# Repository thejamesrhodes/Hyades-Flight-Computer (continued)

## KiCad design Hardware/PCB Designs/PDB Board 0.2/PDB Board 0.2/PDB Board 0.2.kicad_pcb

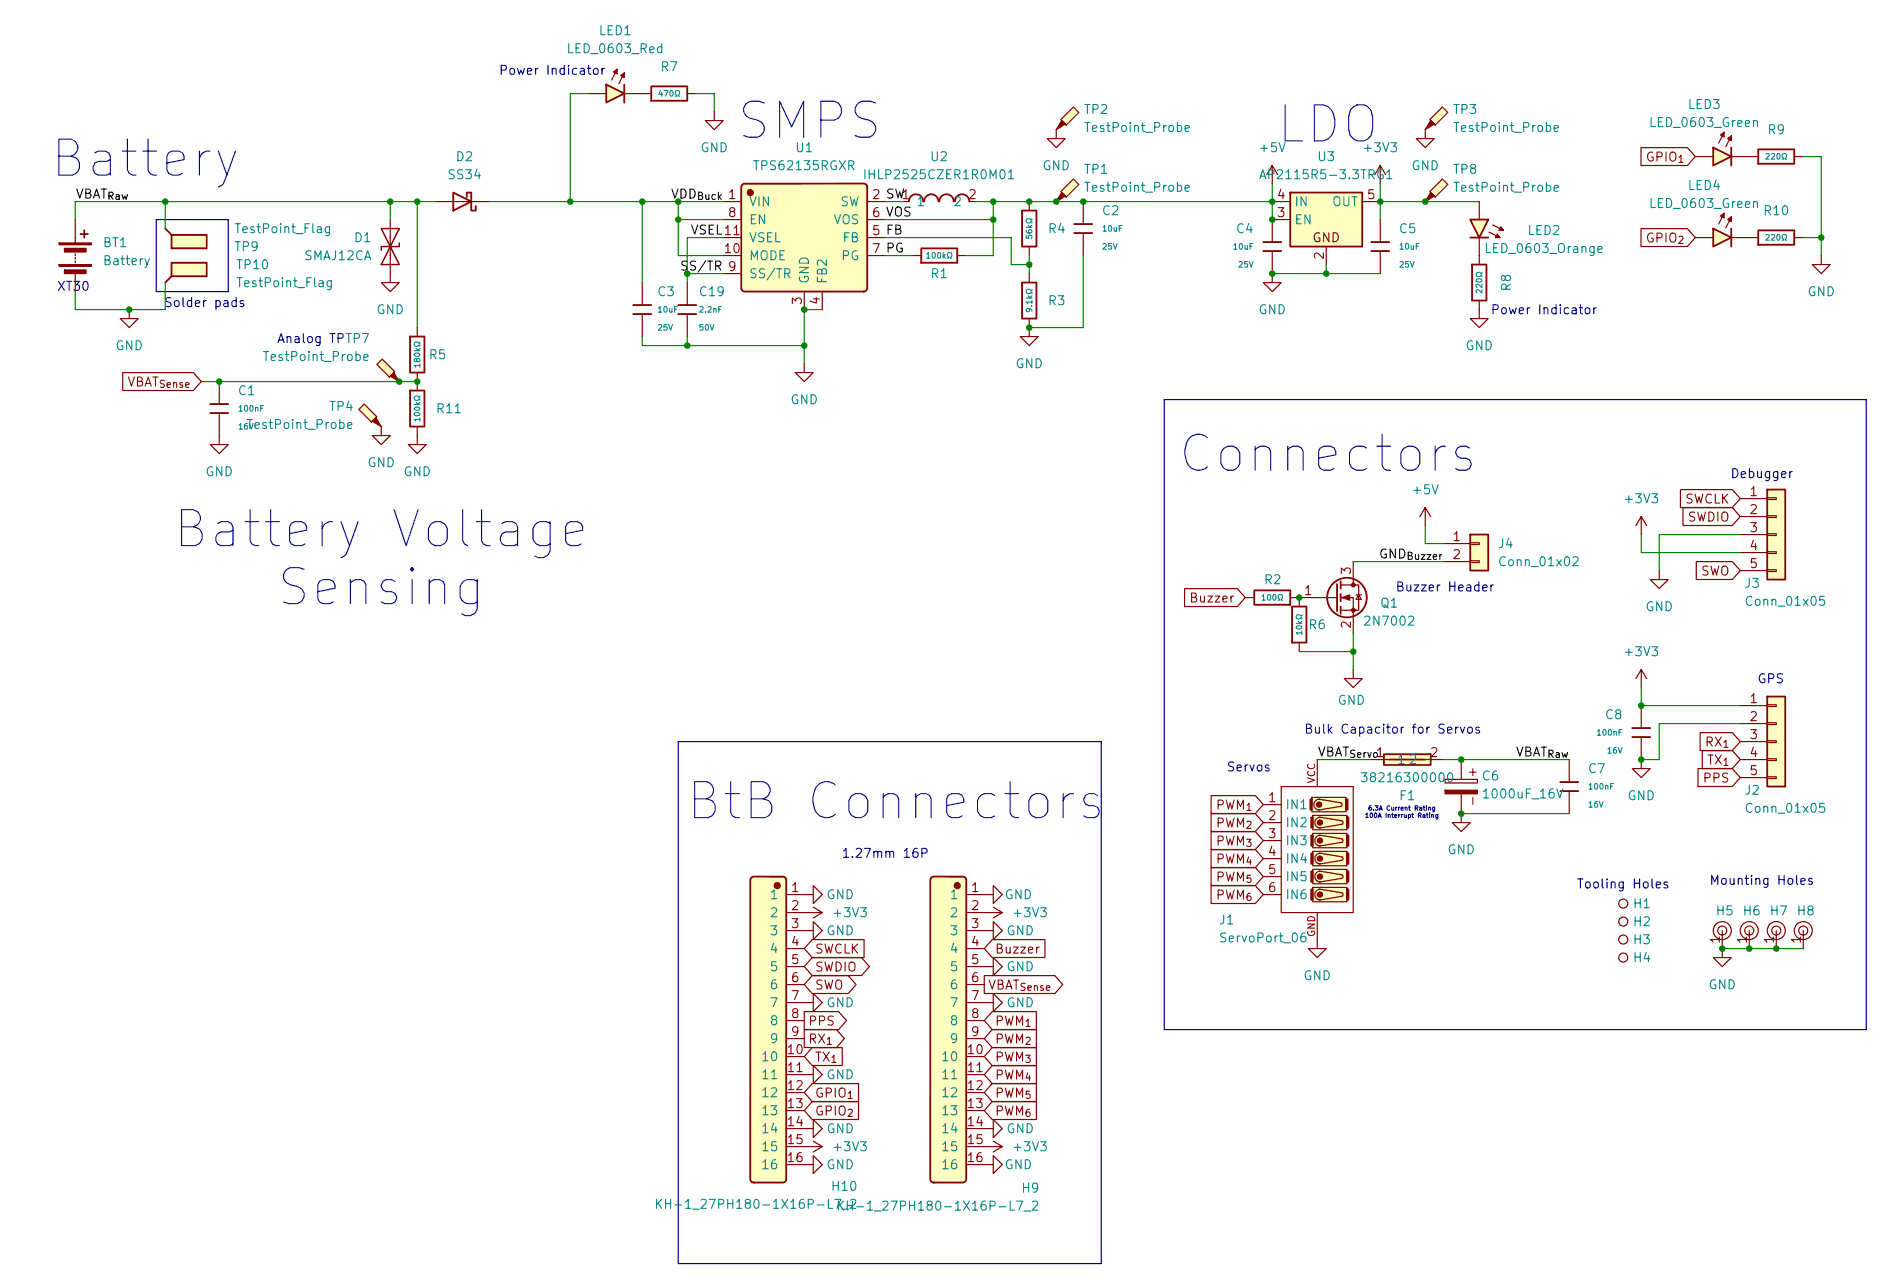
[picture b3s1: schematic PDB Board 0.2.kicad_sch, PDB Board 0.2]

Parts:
BT1: Battery; AMASS_XT30UPB-F_1x02_P5.0mm_Vertical
C1, C7, C8: 100nF; C_0402; Voltage Rated 16V; Tolerance ±10%; Part CL05B104KO5NNNC; LCSC C1525
C2, C3, C4, C5: 10uF; C_0805; Voltage Rated 25V; Tolerance ±10%; Part CL21A106KAYNNNE; LCSC C15850
C6: 1000uF_16V; CP_Radial_D10.0mm_P5.00mm
C19: 2.2nF; C_0402; Voltage Rated 50V; Tolerance ±10%; Part 0402B222K500NT; LCSC C1531
D1: SMAJ12CA; D_SMA
D2: SS34; D_SMA
F1: 38216300000; Manufacturer Part 38216300000; LCSC C142713
H1, H2, H3, H4: Hole_Tooling_JLCPCB
H5, H6, H7, H8: Hole, 3mm
H9, H10: KH-1_27PH180-1X16P-L7_2; Manufacturer Part KH-1.27PH180-1X16P-L7.2; LCSC C2938407
J1: ServoPort_06; ServoPort_06_Vertical
J2, J3: Conn_01x05; JST_XH_B5B-XH-A_1x05_P2.50mm_Vertical
J4: Conn_01x02; JST_XH_B2B-XH-A_1x02_P2.50mm_Vertical; Part Number 1-0201FBV0T
LED1: LED_0603_Red; LED_0603_1608Metric
LED2: LED_0603_Orange; LED_0603_1608Metric
LED3, LED4: LED_0603_Green; LED_0603_1608Metric
Q1: 2N7002; SOT-23
R1, R11: 100kΩ; R_0402; Overload Voltage (Max) 50V; Tolerance ±1%; Part 0402WGF1003TCE; LCSC C25741
R2: 100Ω; R_0402; Overload Voltage (Max) 50V; Tolerance ±1%; Part 0402WGF1000TCE; LCSC C25076
R3: 9.1kΩ; R_0603; Overload Voltage (Max) 75V; Tolerance ±1%; Part 0603WAF9101T5E; LCSC C23260
R4: 56kΩ; R_0603; Overload Voltage (Max) 75V; Tolerance ±1%; Part 0603WAF5602T5E; LCSC C23206
R5: 180kΩ; R_0603; Overload Voltage (Max) 75V; Tolerance ±1%; Part 0603WAF1803T5E; LCSC C22827
R6: 10kΩ; R_0402; Overload Voltage (Max) 50V; Tolerance ±1%; Part 0402WGF1002TCE; LCSC C25744
R7: 470Ω; R_0402; Overload Voltage (Max) 50V; Tolerance ±1%; Part 0402WGF4700TCE; LCSC C25117
R8, R9, R10: 220Ω; R_0402; Overload Voltage (Max) 50V; Tolerance ±1%; Part 0402WGF2200TCE; LCSC C25091
TP1, TP2, TP3, TP4, TP7, TP8: TestPoint_Probe; TestPoint_Pad_04
TP9, TP10: TestPoint_Flag; SolderWirePad_1x01_SMD_4x8mm
U1: TPS62135RGXR; Manufacturer Part TPS62135RGXR; LCSC C167238
U2: IHLP2525CZER1R0M01; Manufacturer Part IHLP2525CZER1R0M01; LCSC C845018
U3: AP2115R5-3.3TRG1; Diodes_SOT-89-5

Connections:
+3V3: C5.1, C8.1, H9.2, H9.15, H10.2, H10.15, J2.1, J3.4, LED2.2 (A), TP8.1 (1_1), U3.5 (OUT)
+5V: C2.1, C4.1, J4.1, R1.2, R4.1, TP1.1 (1_1), U1.6 (VOS), U2.2, U3.3 (EN), U3.4 (IN)
/FB: R3.1, R4.2, U1.5 (FB)
/GND_{Buzzer}: J4.2, Q1.3 (D)
/PG: R1.1, U1.7 (PG)
/SS/TR: C19.1, U1.9 (SS/TR), U1.11 (VSEL)
/SW: U1.2 (SW), U2.1
/VBAT_{Raw}: BT1.1 (+), C6.1, C7.1, D1.2 (A2), D2.2 (A), F1.2, R5.1, TP9.1 (1_1)
/VBAT_{Servo}: F1.1, J1.VCC
/VDD_{Buck}: C3.1, D2.1 (K), LED1.2 (A), U1.1 (VIN), U1.8 (EN), U1.10 (MODE)
Buzzer: H9.4, R2.2
GND: BT1.2 (-), C1.2, C2.2, C3.2, C4.2, C5.2, C6.2, C7.2, C8.2, C19.2, D1.1 (A1), H5.1, H6.1, H7.1, H8.1, H9.1, H9.3, H9.5, H9.7, H9.14, H9.16, H10.1, H10.3, H10.7, H10.11, H10.14, H10.16, J1.GND, J2.2, J3.3, Q1.2 (S), R3.2, R6.1, R7.2, R8.2, R9.2, R10.2, R11.2, TP2.1 (1_1), TP3.1 (1_1), TP4.1 (1_1), TP10.1 (1_1), U1.3 (GND), U1.4 (FB2), U3.2
GPIO_{1}: H10.12, LED3.2 (A)
GPIO_{2}: H10.13, LED4.2 (A)
unnamed: LED1.1 (K), R7.1
unnamed: LED2.1 (K), R8.1
unnamed: LED3.1 (K), R9.1
unnamed: LED4.1 (K), R10.1
unnamed: Q1.1 (G), R2.1, R6.2
PPS: H10.8, J2.5
PWM_{1}: H9.8, J1.1 (IN1)
PWM_{2}: H9.9, J1.2 (IN2)
PWM_{3}: H9.10, J1.3 (IN3)
PWM_{4}: H9.11, J1.4 (IN4)
PWM_{5}: H9.12, J1.5 (IN5)
PWM_{6}: H9.13, J1.6 (IN6)
RX_{1}: H10.9, J2.3
SWCLK: H10.4, J3.1
SWDIO: H10.5, J3.2
SWO: H10.6, J3.5
TX_{1}: H10.10, J2.4
VBAT_{Sense}: C1.1, H9.6, R5.2, R11.1, TP7.1 (1_1)

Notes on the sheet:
Solder pads
BtB Connectors
XT30
6.3A Current Rating 100A Interrupt Rating
Servos
SMPS
Power Indicator
Bulk Capacitor for Servos
Connectors
Analog TP
1.27mm 16P
Mounting Holes
LDO
Battery
Buzzer Header
Battery Voltage Sensing
GPS
Debugger
Tooling Holes

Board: 4 copper layers, 54 parts (2 on the bottom side), 32 nets, no tracks yet.

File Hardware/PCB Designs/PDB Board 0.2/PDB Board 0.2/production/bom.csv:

Designator,Footprint,Quantity,Value,LCSC Part #
BT1,AMASS_XT30UPB-F_1x02_P5.0mm_Vertical,1,Battery,
"C1, C7, C8",C_0402,3,100nF,C1525
C19,C_0402,1,2.2nF,C1531
"C2, C3, C4, C5",C_0805,4,10uF,C15850
C6,CP_Radial_D10.0mm_P5.00mm,1,1000uF_16V,
D1,D_SMA,1,SMAJ12CA,
D2,D_SMA,1,SS34,
F1,38216300000,1,38216300000,C142713
"H1, H2, H3, H4",Hole_Tooling_JLCPCB,4,~,
"H10, H9",KH-1_27PH180-1X16P-L7_2,2,KH-1_27PH180-1X16P-L7_2,C2938407
"H5, H6, H7, H8","Hole, 3mm",4,~,
J1,ServoPort_06_Vertical,1,ServoPort_06,
"J2, J3",JST_XH_B5B-XH-A_1x05_P2.50mm_Vertical,2,Conn_01x05,
J4,JST_XH_B2B-XH-A_1x02_P2.50mm_Vertical,1,Conn_01x02,
LED1,0603,1,LED_0603_Red,
LED2,0603,1,LED_0603_Orange,
"LED3, LED4",0603,2,LED_0603_Green,
Q1,SOT-23,1,2N7002,
"R1, R11",R_0402,2,100kΩ,C25741
"R10, R8, R9",R_0402,3,220Ω,C25091
R2,R_0402,1,100Ω,C25076
R3,R_0603,1,9.1kΩ,C23260
R4,R_0603,1,56kΩ,C23206
R5,R_0603,1,180kΩ,C22827
R6,R_0402,1,10kΩ,C25744
R7,R_0402,1,470Ω,C25117
"TP1, TP2, TP3, TP4, TP7, TP8",TestPoint_Pad_04,6,TestPoint_Probe,
"TP10, TP9",SolderWirePad_1x01_SMD_4x8mm,2,TestPoint_Flag,
U1,TPS62135RGXR,1,TPS62135RGXR,C167238
U2,IHLP2525CZER1R0M01,1,IHLP2525CZER1R0M01,C845018
U4,Diodes_SOT-89-5,1,AP2115R5A-3.3TRG1,

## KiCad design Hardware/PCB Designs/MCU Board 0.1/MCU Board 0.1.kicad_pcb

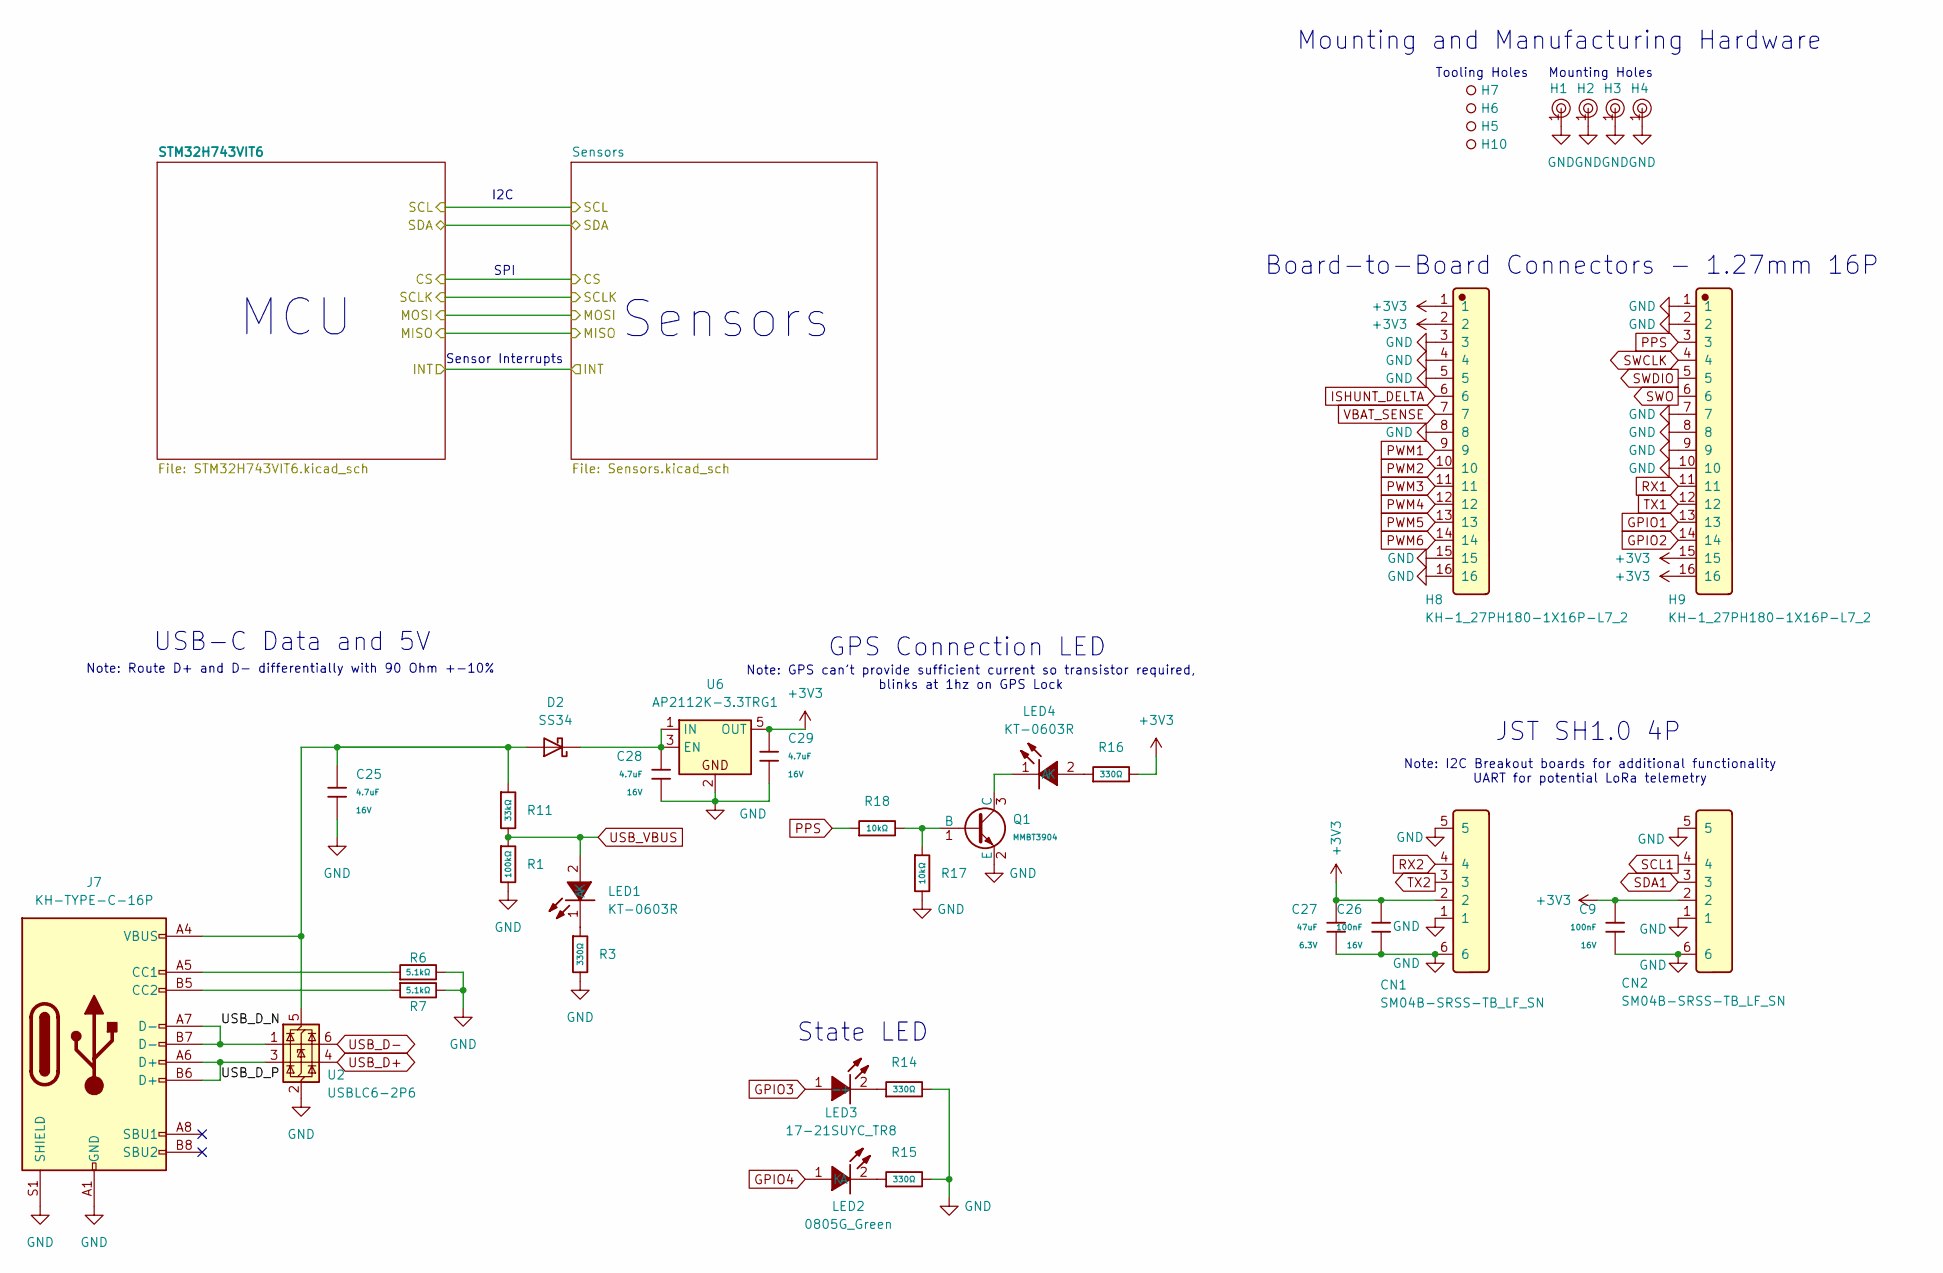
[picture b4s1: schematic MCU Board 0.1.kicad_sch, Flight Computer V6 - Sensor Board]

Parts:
C9, C26: 100nF; C_0402; Voltage Rated 16V; Tolerance ±10%; Part CL05B104KO5NNNC; LCSC C1525
C25, C28, C29: 4.7uF; C_0603; Voltage Rated 16V; Tolerance ±10%; Part CL10A475KO8NNNC; LCSC C19666
C27: 47uF; C_0805; Voltage Rated 6.3V; Tolerance ±20%; Part CL21A476MQYNNNE; LCSC C16780
CN1, CN2: SM04B-SRSS-TB_LF_SN; Manufacturer Part SM04B-SRSS-TB(LF)(SN); LCSC C160404
D2: SS34; D_SMA
H1, H2, H3, H4: Hole, 3mm
H5, H6, H7, H10: Hole_Tooling_JLCPCB
H8, H9: KH-1_27PH180-1X16P-L7_2; Manufacturer Part KH-1.27PH180-1X16P-L7.2; LCSC C2938407
J7: KH-TYPE-C-16P
LED1, LED4: KT-0603R; Manufacturer Part KT-0603R; LCSC C2286
LED2: 0805G_Green; Manufacturer Part KT-0805G; LCSC C2297
LED3: 17-21SUYC_TR8; Manufacturer Part KT-0805黄灯; LCSC C2296
Q1: MMBT3904; Q_SOT-23; Part MMBT3904; LCSC C7420353
R1: 100kΩ; R_0402; Overload Voltage (Max) 50V; Tolerance ±1%; Part 0402WGF1003TCE; LCSC C25741
R3, R14, R15, R16: 330Ω; R_0402; Overload Voltage (Max) 50V; Tolerance ±1%; Part 0402WGF3300TCE; LCSC C25104
R6, R7: 5.1kΩ; R_0402; Overload Voltage (Max) 50V; Tolerance ±1%; Part 0402WGF5101TCE; LCSC C25905
R11: 33kΩ; R_0402; Overload Voltage (Max) 50V; Tolerance ±1%; Part 0402WGF3302TCE; LCSC C25779
R17, R18: 10kΩ; R_0402; Overload Voltage (Max) 50V; Tolerance ±1%; Part 0402WGF1002TCE; LCSC C25744
U2: USBLC6-2P6; SOT-666
U6: AP2112K-3.3TRG1; SOT-23-5

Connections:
+3V3: C9.1, C26.1, C27.1, C29.1, CN1.2, CN2.2, H8.1, H8.2, H9.15, H9.16, R16.2, U6.5 (OUT); also elsewhere on the board
/USB_D_N: J7.A7 (D-), J7.B7 (D-), U2.1 (I/O1)
/USB_D_P: J7.A6 (D+), J7.B6 (D+), U2.3 (I/O2)
GND: C9.2, C25.2, C26.2, C27.2, C28.2, C29.2, CN1.1, CN1.5, CN1.6, CN2.1, CN2.5, CN2.6, H1.1, H2.1, H3.1, H4.1, H8.3, H8.4, H8.5, H8.8, H8.15, H8.16, H9.1, H9.2, H9.7, H9.8, H9.9, H9.10, J7.A1 (GND), J7.A12 (GND), J7.B1 (GND), J7.B12 (GND), J7.S1 (SHIELD), Q1.2 (E), R1.2, R3.2, R6.2, R7.2, R14.2, R15.2, R17.2, U2.2 (GND), U6.2; also elsewhere on the board
GPIO1: H9.13; also elsewhere on the board
GPIO2: H9.14; also elsewhere on the board
GPIO3: LED3.1 (+); also elsewhere on the board
GPIO4: LED2.1 (A); also elsewhere on the board
ISHUNT_DELTA: H8.6; also elsewhere on the board
unnamed: C25.1, D2.2 (A), J7.A4 (VBUS), J7.A9 (VBUS), J7.B4 (VBUS), J7.B9 (VBUS), R11.1, U2.5 (VBUS)
unnamed: C28.1, D2.1 (K), U6.1 (IN), U6.3 (EN)
unnamed: J7.A5 (CC1), R6.1
unnamed: J7.B5 (CC2), R7.1
unnamed: LED1.1 (K), R3.1
unnamed: LED2.2 (K), R15.1
unnamed: LED3.2 (-), R14.1
unnamed: LED4.2 (A), R16.1
unnamed: LED4.1 (K), Q1.3 (C)
unnamed: Q1.1 (B), R17.1, R18.2
PPS: H9.3, R18.1; also elsewhere on the board
PWM1: H8.9; also elsewhere on the board
PWM2: H8.10; also elsewhere on the board
PWM3: H8.11; also elsewhere on the board
PWM4: H8.12; also elsewhere on the board
PWM5: H8.13; also elsewhere on the board
PWM6: H8.14; also elsewhere on the board
RX1: H9.11; also elsewhere on the board
RX2: CN1.4; also elsewhere on the board
SCL1: CN2.4; also elsewhere on the board
SDA1: CN2.3; also elsewhere on the board
SWCLK: H9.4; also elsewhere on the board
SWDIO: H9.5; also elsewhere on the board
SWO: H9.6; also elsewhere on the board
TX1: H9.12; also elsewhere on the board
TX2: CN1.3; also elsewhere on the board
USB_D+: U2.4 (I/O2); also elsewhere on the board
USB_D-: U2.6 (I/O1); also elsewhere on the board
USB_VBUS: LED1.2 (A), R1.1, R11.2; also elsewhere on the board
VBAT_SENSE: H8.7; also elsewhere on the board

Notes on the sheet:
Tooling Holes
Sensor Interrupts
Sensors
Board-to-Board Connectors - 1.27mm 16P
GPS Connection LED
State LED
USB-C Data and 5V
Note: Route D+ and D- differentially with 90 Ohm +-10%
Note: GPS can't provide sufficient current so transistor required, blinks at 1hz on GPS Lock
JST SH1.0 4P
Note: I2C Breakout boards for additional functionality UART for potential LoRa telemetry
SPI
I2C
Mounting and Manufacturing Hardware
Mounting Holes
MCU

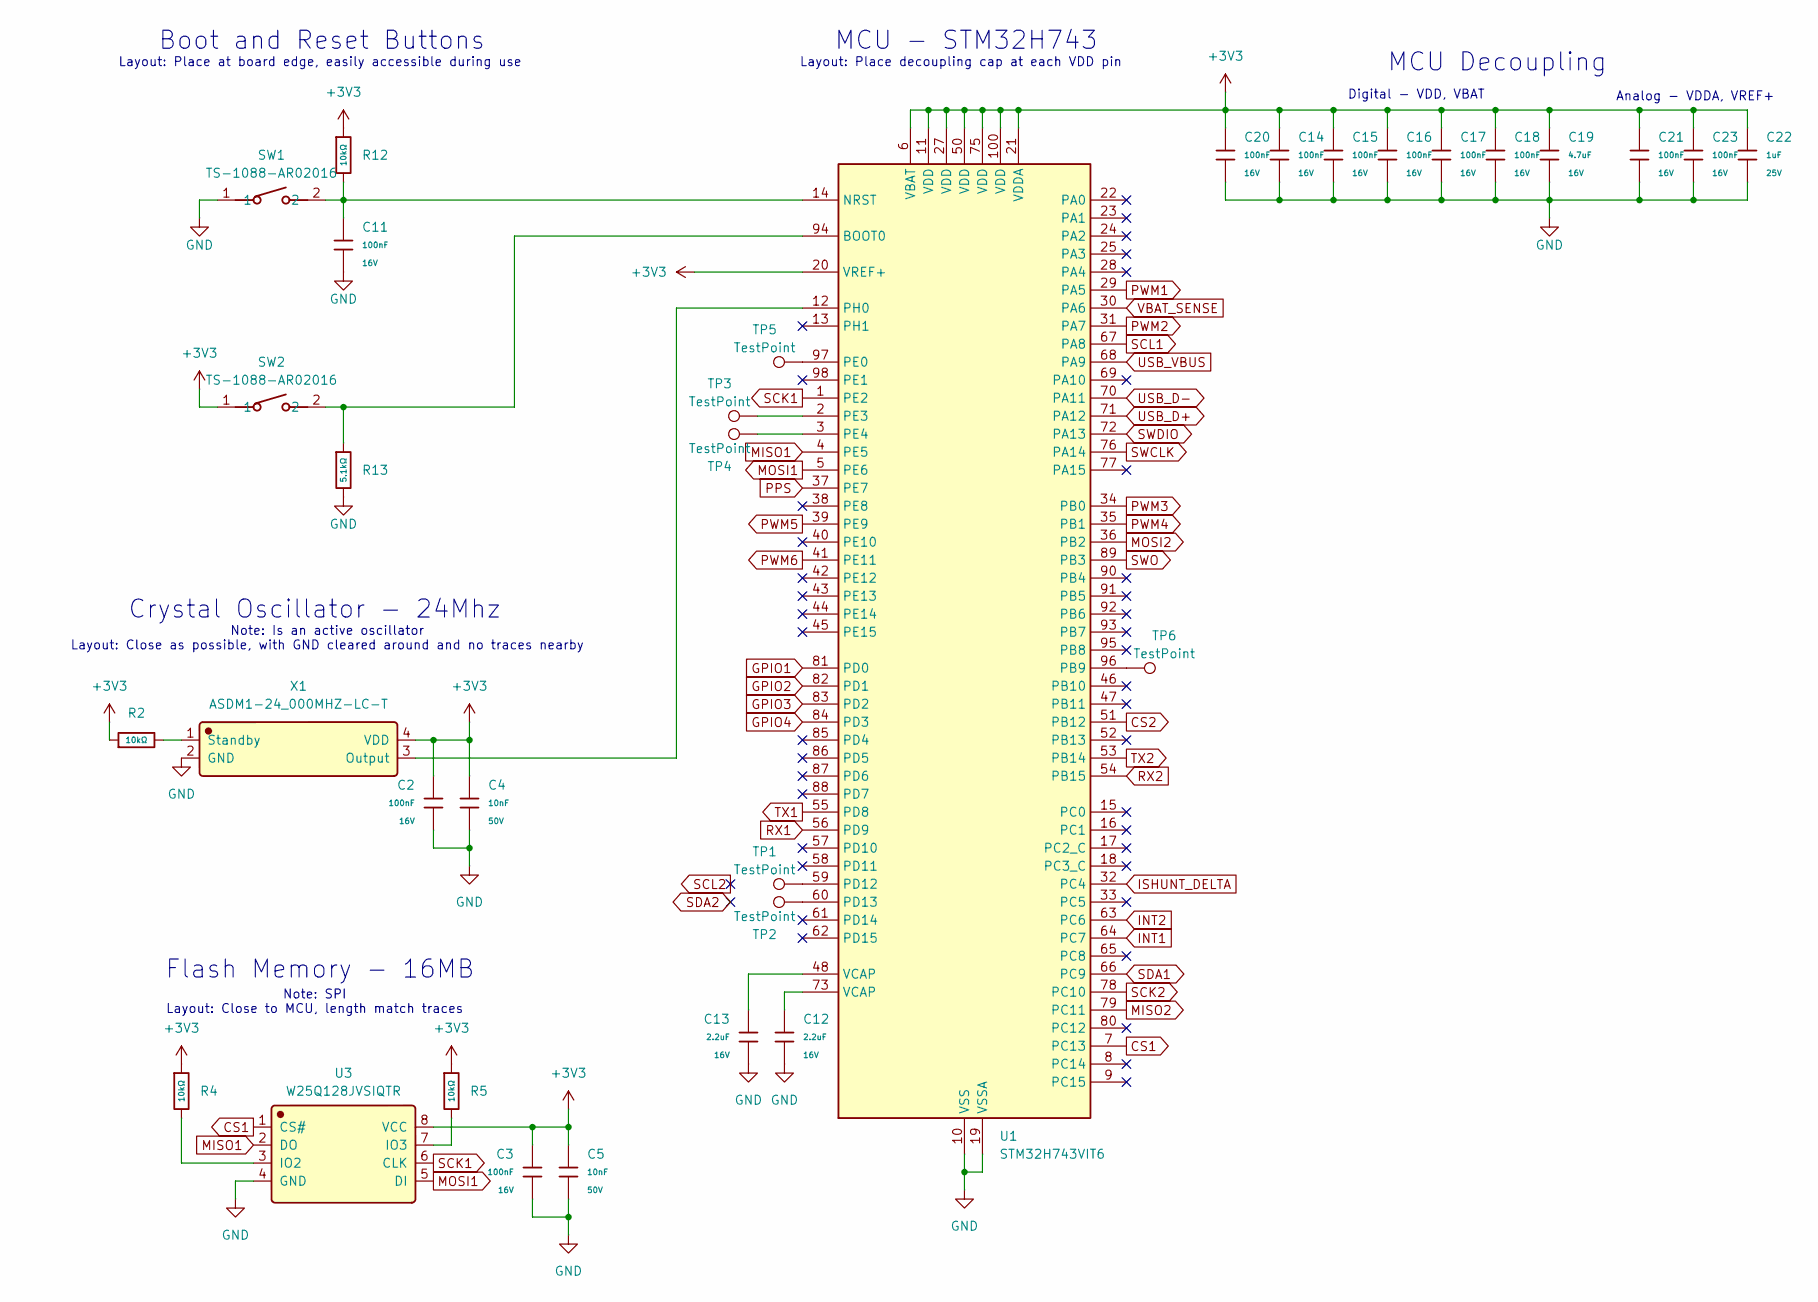
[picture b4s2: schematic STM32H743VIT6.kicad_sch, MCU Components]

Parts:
C2, C3, C11, C14, C15, C16, C17, C18, C20, C21, C23: 100nF; C_0402; Voltage Rated 16V; Tolerance ±10%; Part CL05B104KO5NNNC; LCSC C1525
C4, C5: 10nF; C_0402; Voltage Rated 50V; Tolerance ±10%; Part CL05B103KB5NNNC; LCSC C15195
C12, C13: 2.2uF; C_0603; Voltage Rated 16V; Tolerance ±10%; Part CL10A225KO8NNNC; LCSC C23630
C19: 4.7uF; C_0603; Voltage Rated 16V; Tolerance ±10%; Part CL10A475KO8NNNC; LCSC C19666
C22: 1uF; C_0402; Voltage Rated 25V; Tolerance ±10%; Part CL05A105KA5NQNC; LCSC C52923
R2: 10kΩ; R_0603; Overload Voltage (Max) 75V; Tolerance ±1%; Part 0603WAF1002T5E; LCSC C25804
R4, R5, R12: 10kΩ; R_0402; Overload Voltage (Max) 50V; Tolerance ±1%; Part 0402WGF1002TCE; LCSC C25744
R13: 5.1kΩ; R_0402; Overload Voltage (Max) 50V; Tolerance ±1%; Part 0402WGF5101TCE; LCSC C25905
SW1, SW2: TS-1088-AR02016; Manufacturer Part TS-1088-AR02016; LCSC C720477
TP1, TP2, TP3, TP4, TP5, TP6: TestPoint; TestPoint_Pad_1.5x1.5mm
U1: STM32H743VIT6; LQFP-100_14x14mm_P0.5mm
U3: W25Q128JVSIQTR; Manufacturer Part W25Q128JVSIQ; LCSC C97521
X1: ASDM1-24_000MHZ-LC-T; Manufacturer Part ASDM1-24.000MHZ-LC-T; LCSC C1987235

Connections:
+3V3: C2.1, C3.1, C4.1, C5.1, C14.1, C15.1, C16.1, C17.1, C18.1, C19.1, C20.1, C21.1, C22.1, C23.1, R2.1, R4.1, R5.1, R12.1, SW2.1, U1.6 (VBAT), U1.11 (VDD), U1.20 (VREF+), U1.21 (VDDA), U1.27 (VDD), U1.50 (VDD), U1.75 (VDD), U1.100 (VDD), U3.8 (VCC), X1.4 (VDD); also elsewhere on the board
CS1: U1.7 (PC13), U3.1 (CS#)
CS2: U1.51 (PB12); also elsewhere on the board
GND: C2.2, C3.2, C4.2, C5.2, C11.2, C12.2, C13.2, C14.2, C15.2, C16.2, C17.2, C18.2, C19.2, C20.2, C21.2, C22.2, C23.2, R13.2, SW1.1, U1.10 (VSS), U1.19 (VSSA), U1.26 (VSS), U1.49 (VSS), U1.74 (VSS), U1.99 (VSS), U3.4 (GND), X1.2 (GND); also elsewhere on the board
GPIO1: U1.81 (PD0); also elsewhere on the board
GPIO2: U1.82 (PD1); also elsewhere on the board
GPIO3: U1.83 (PD2); also elsewhere on the board
GPIO4: U1.84 (PD3); also elsewhere on the board
INT1: U1.64 (PC7); also elsewhere on the board
INT2: U1.63 (PC6); also elsewhere on the board
ISHUNT_DELTA: U1.32 (PC4); also elsewhere on the board
MISO1: U1.4 (PE5), U3.2 (DO)
MISO2: U1.79 (PC11); also elsewhere on the board
MOSI1: U1.5 (PE6), U3.5 (DI)
MOSI2: U1.36 (PB2); also elsewhere on the board
unnamed: C12.1, U1.73 (VCAP)
unnamed: C13.1, U1.48 (VCAP)
unnamed: R13.1, SW2.2, U1.94 (BOOT0)
unnamed: C11.1, R12.2, SW1.2, U1.14 (NRST)
unnamed: TP6.1 (1_1), U1.96 (PB9)
unnamed: TP1.1 (1_1), U1.59 (PD12)
unnamed: TP2.1 (1_1), U1.60 (PD13)
unnamed: TP5.1 (1_1), U1.97 (PE0)
unnamed: TP3.1 (1_1), U1.2 (PE3)
unnamed: TP4.1 (1_1), U1.3 (PE4)
unnamed: U1.12 (PH0), X1.3 (Output)
unnamed: R4.2, U3.3 (IO2)
unnamed: R5.2, U3.7 (IO3)
unnamed: R2.2, X1.1 (Standby)
PPS: U1.37 (PE7); also elsewhere on the board
PWM1: U1.29 (PA5); also elsewhere on the board
PWM2: U1.31 (PA7); also elsewhere on the board
PWM3: U1.34 (PB0); also elsewhere on the board
PWM4: U1.35 (PB1); also elsewhere on the board
PWM5: U1.39 (PE9); also elsewhere on the board
PWM6: U1.41 (PE11); also elsewhere on the board
RX1: U1.56 (PD9); also elsewhere on the board
RX2: U1.54 (PB15); also elsewhere on the board
SCK1: U1.1 (PE2), U3.6 (CLK)
SCK2: U1.78 (PC10); also elsewhere on the board
SCL1: U1.67 (PA8); also elsewhere on the board
SDA1: U1.66 (PC9); also elsewhere on the board
SWCLK: U1.76 (PA14); also elsewhere on the board
SWDIO: U1.72 (PA13); also elsewhere on the board
SWO: U1.89 (PB3); also elsewhere on the board
TX1: U1.55 (PD8); also elsewhere on the board
TX2: U1.53 (PB14); also elsewhere on the board
USB_D+: U1.71 (PA12); also elsewhere on the board
USB_D-: U1.70 (PA11); also elsewhere on the board
USB_VBUS: U1.68 (PA9); also elsewhere on the board
VBAT_SENSE: U1.30 (PA6); also elsewhere on the board

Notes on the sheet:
Note: SPI Layout: Close to MCU, length match traces
Flash Memory - 16MB
Crystal Oscillator - 24Mhz
MCU Decoupling
Layout: Place decoupling cap at each VDD pin
Boot and Reset Buttons
Analog - VDDA, VREF+
MCU - STM32H743
Digital - VDD, VBAT
Note: Is an active oscillator Layout: Close as possible, with GND cleared around and no traces nearby
Layout: Place at board edge, easily accessible during use

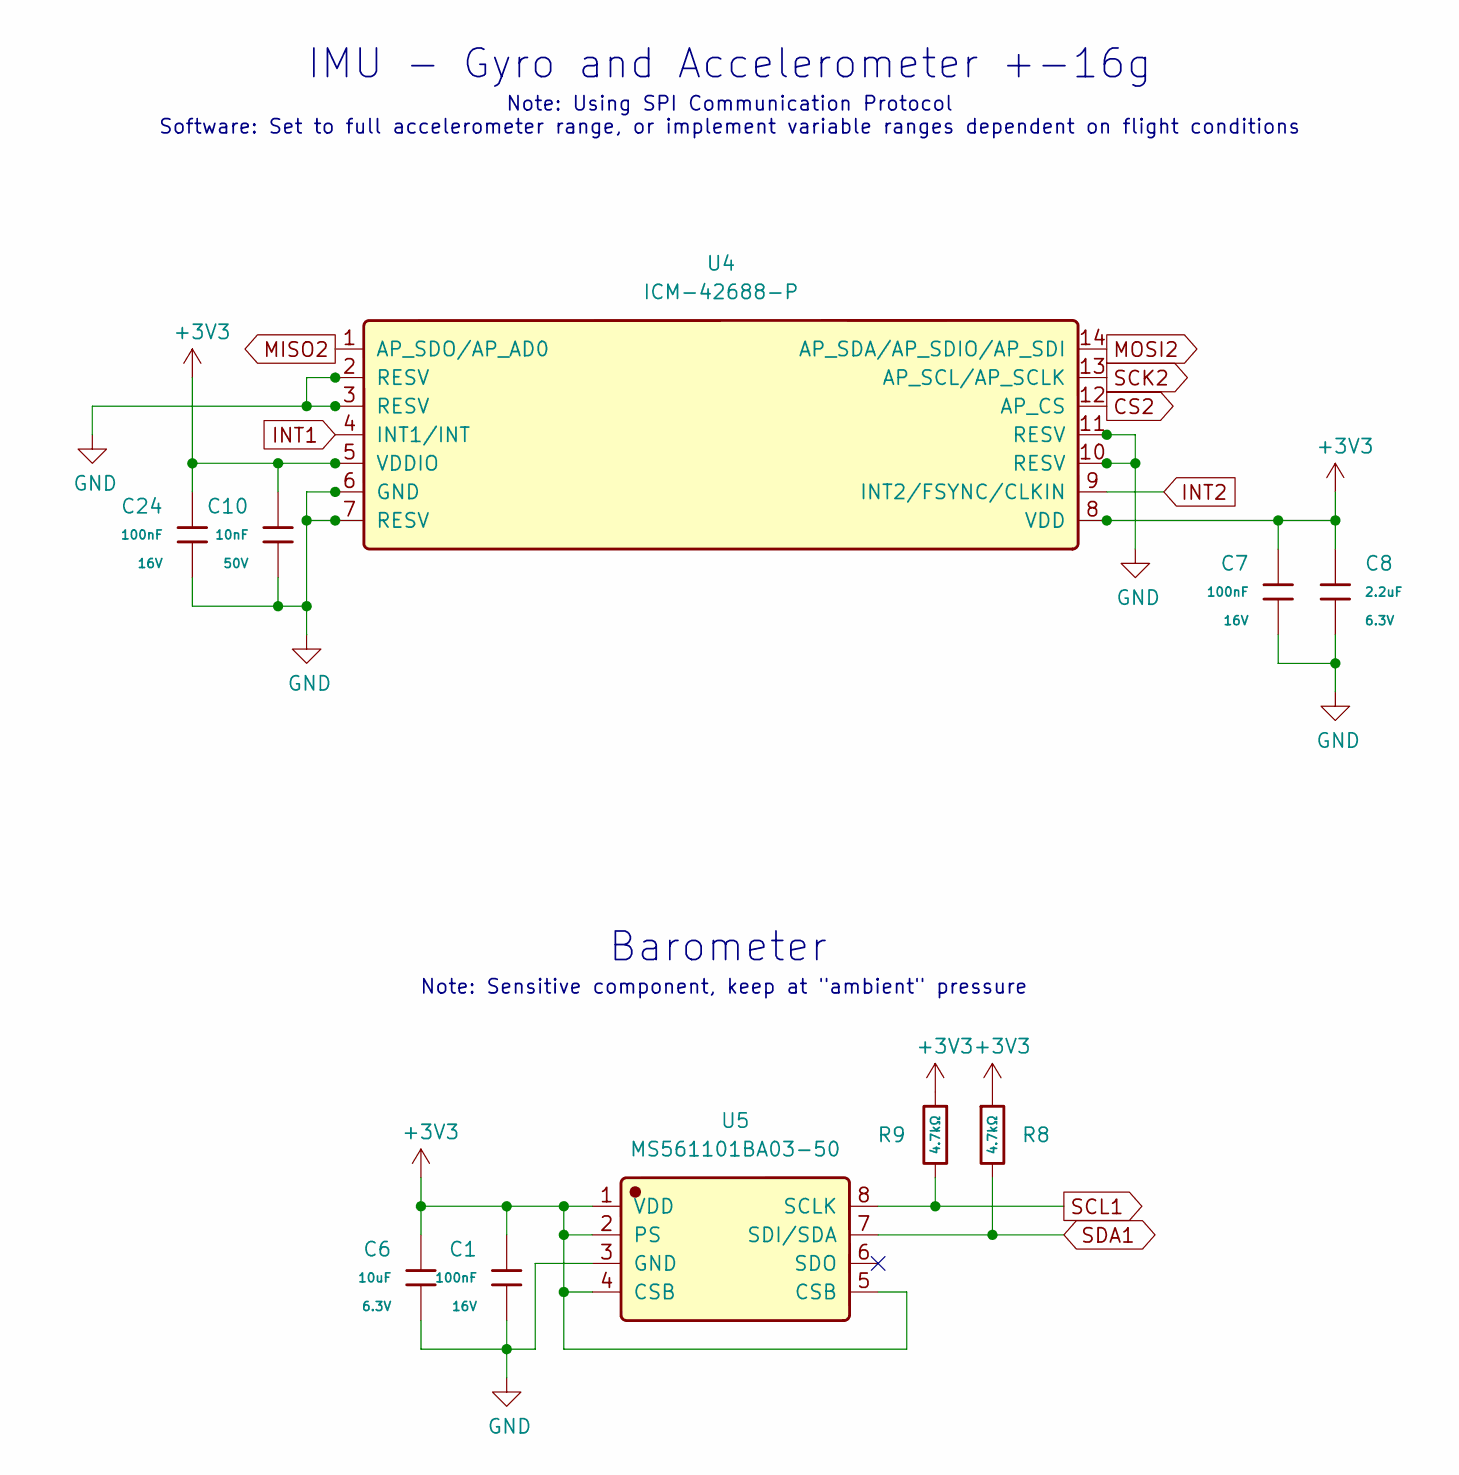
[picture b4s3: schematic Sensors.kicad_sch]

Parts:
C1, C7, C24: 100nF; C_0402; Voltage Rated 16V; Tolerance ±10%; Part CL05B104KO5NNNC; LCSC C1525
C6: 10uF; C_0402; Voltage Rated 6.3V; Tolerance ±20%; Part CL05A106MQ5NUNC; LCSC C15525
C8: 2.2uF; C_0402; Voltage Rated 6.3V; Tolerance ±20%; Part CL05A225MQ5NSNC; LCSC C12530
C10: 10nF; C_0402; Voltage Rated 50V; Tolerance ±10%; Part CL05B103KB5NNNC; LCSC C15195
R8, R9: 4.7kΩ; R_0603; Overload Voltage (Max) 75V; Tolerance ±1%; Part 0603WAF4701T5E; LCSC C23162
U4: ICM-42688-P; Manufacturer Part ICM-42688-P; LCSC C1850418
U5: MS561101BA03-50; Manufacturer Part MS561101BA03-50; LCSC C15639

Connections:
+3V3: C1.1, C6.1, C7.1, C8.1, C10.1, C24.1, R8.1, R9.1, U4.5 (VDDIO), U4.8 (VDD), U5.1 (VDD), U5.2 (PS), U5.4 (CSB), U5.5 (CSB); also elsewhere on the board
CS2: U4.12 (AP_CS); also elsewhere on the board
GND: C1.2, C6.2, C7.2, C8.2, C10.2, C24.2, U4.2 (RESV), U4.3 (RESV), U4.6 (GND), U4.7 (RESV), U4.10 (RESV), U4.11 (RESV), U5.3 (GND); also elsewhere on the board
INT1: U4.4 (INT1/INT); also elsewhere on the board
INT2: U4.9 (INT2/FSYNC/CLKIN); also elsewhere on the board
MISO2: U4.1 (AP_SDO/AP_AD0); also elsewhere on the board
MOSI2: U4.14 (AP_SDA/AP_SDIO/AP_SDI); also elsewhere on the board
SCK2: U4.13 (AP_SCL/AP_SCLK); also elsewhere on the board
SCL1: R9.2, U5.8 (SCLK); also elsewhere on the board
SDA1: R8.2, U5.7 (SDI/SDA); also elsewhere on the board

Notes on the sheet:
Note: Using SPI Communication Protocol Software: Set to full accelerometer range, or implement variable ranges dependent on flight conditions
Note: Sensitive component, keep at "ambient" pressure
IMU - Gyro and Accelerometer +-16g
Barometer

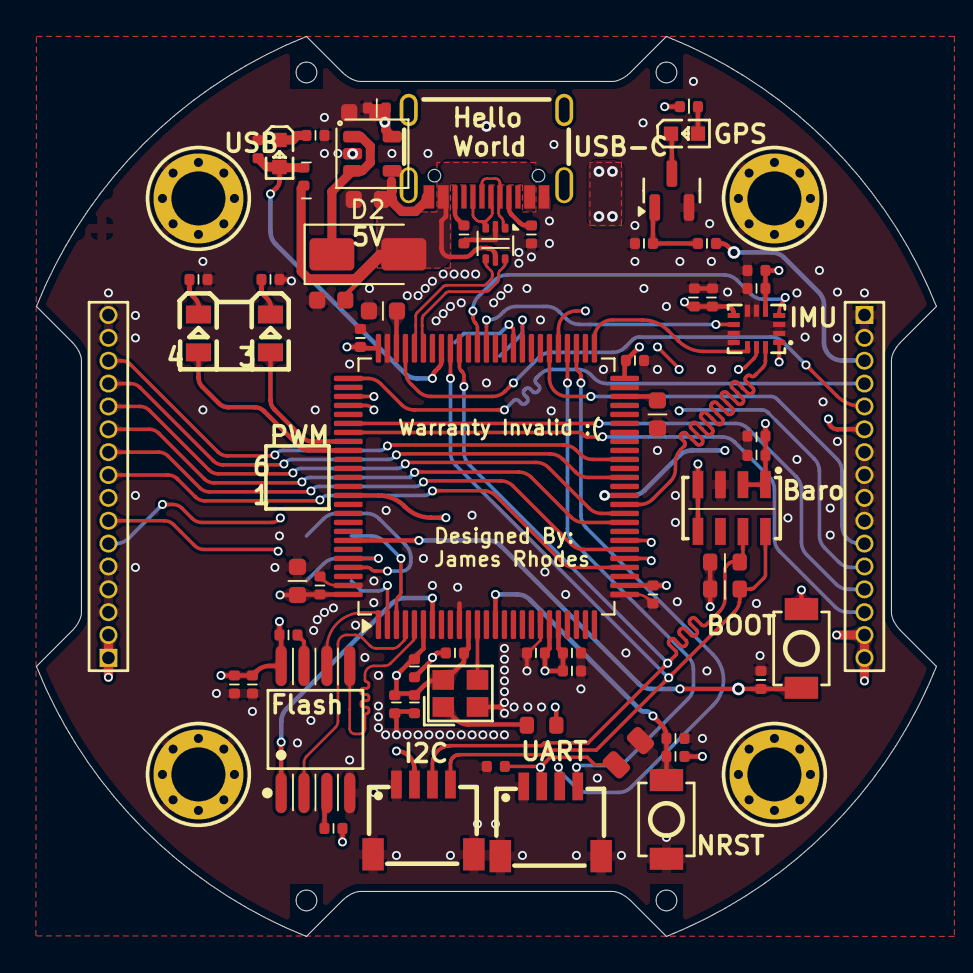
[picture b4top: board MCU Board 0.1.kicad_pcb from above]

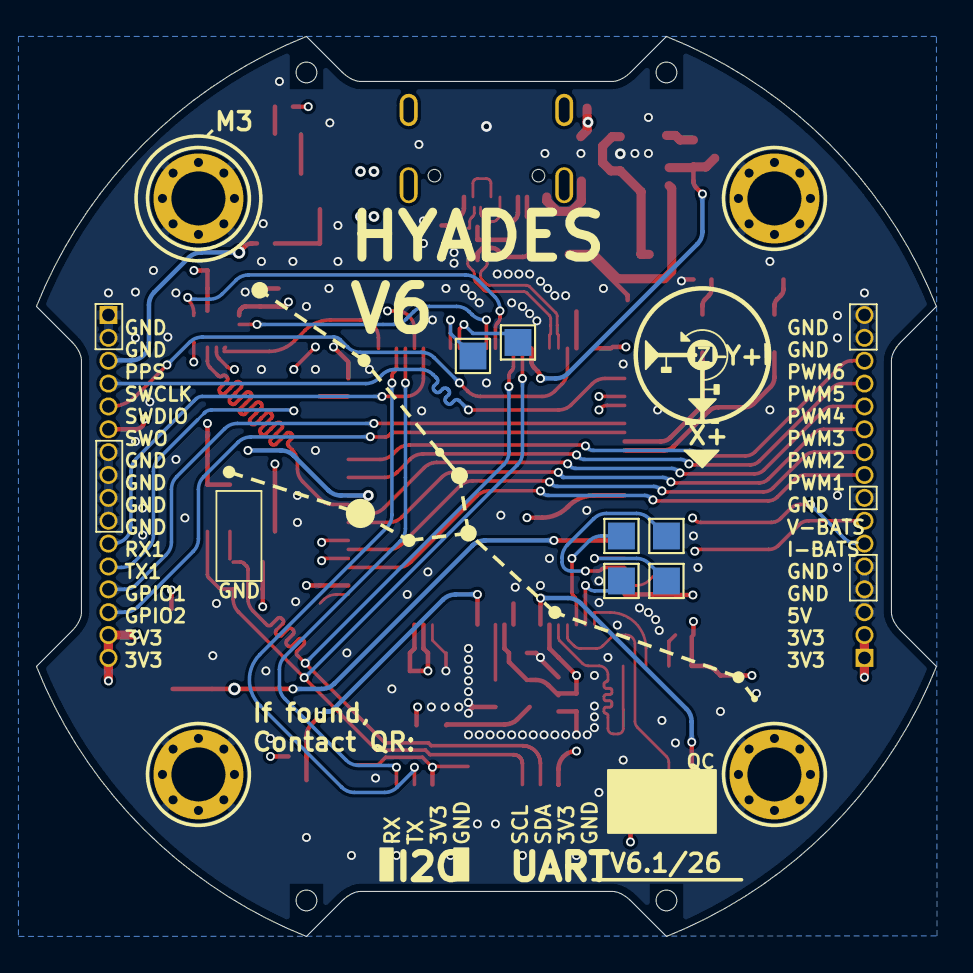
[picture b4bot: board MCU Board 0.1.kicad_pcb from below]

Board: 4 copper layers, 50.0 x 50.0 mm, 80 parts (6 on the bottom side), 63 nets.

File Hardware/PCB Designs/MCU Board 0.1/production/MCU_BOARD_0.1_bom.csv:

Designator,Footprint,Quantity,Value,LCSC Part #
"C1, C11, C14, C15, C16, C17, C18, C2, C20, C21, C23, C24, C3, C7",C_0402,14,100nF,C1525
"C10, C4, C5",C_0402,3,10nF,C15195
"C12, C13",C_0603,2,2.2uF,C23630
C19,C_0603,1,4.7uF,C19666
C22,C_0402,1,1uF,C52923
C6,C_0402,1,10uF,C15525
C8,C_0402,1,2.2uF,C12530
C9,C_0603,1,10uF,
"CN1, CN2",SM04B-SRSS-TB_LF_SN,2,SM04B-SRSS-TB_LF_SN,C160404
D1,D_SMF,1,SMF6V5A,
"H1, H2, H3, H4","Hole, 3mm",4,~,
"H10, H5, H6, H7",Hole_Tooling_JLCPCB,4,~,
"H8, H9",KH-1_27PH180-1X16P-L7_2,2,KH-1_27PH180-1X16P-L7_2,C2938407
J7,KH-TYPE-C-16P,1,KH-TYPE-C-16P,C709357
"LED1, LED4",KT-0603R,2,KT-0603R,C2286
LED2,0805G_Green,1,0805G_Green,C2297
LED3,17-21SUYC_TR8,1,17-21SUYC_TR8,C2296
Q1,Q_SOT-23,1,MMBT3904,C7420353
R1,R_0402,1,100kΩ,C25741
"R12, R17, R18, R2, R4, R5",R_0402,6,10kΩ,C25744
"R13, R6, R7",R_0402,3,5.1kΩ,C25905
"R14, R15, R16, R3",R_0402,4,330Ω,C25104
"R8, R9",R_0603,2,4.7kΩ,C23162
"SW1, SW2",TS-1088-AR02016,2,TS-1088-AR02016,C720477
"TP1, TP2, TP3, TP4, TP5, TP6",TestPoint_Pad_1.5x1.5mm,6,TestPoint,
U1,LQFP-100_14x14mm_P0.5mm,1,STM32H743VIT6,
U2,SOT-666,1,USBLC6-2P6,
U3,W25Q128JVSIQTR,1,W25Q128JVSIQTR,C97521
U4,ICM-42688-P,1,ICM-42688-P,C1850418
U5,MS561101BA03-50,1,MS561101BA03-50,C15639
X1,ASDM1-24_000MHZ-LC-T,1,ASDM1-24_000MHZ-LC-T,C1987235
